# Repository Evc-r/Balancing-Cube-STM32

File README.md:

# STM32F411/ICM-20948 v2 Self-Balancing Cube

Firmware and integration work for a three-axis reaction-wheel balancing cube based on the open-source [remrc/Self-Balancing-Cube](https://github.com/remrc/Self-Balancing-Cube) project.

This version replaces the original ESP32 and MPU6050 with:

- **STM32F411CEU6** microcontroller
- **ICM-20948 v2 breakout** intelligent IMU
- Three **Nidec 24H** reaction-wheel motors with integrated drivers and quadrature encoders
- **3S LiPo** power system

> [!WARNING]
> This project contains high-speed reaction wheels and a LiPo battery. Incorrect PWM polarity, wiring, firmware, or mechanical assembly can cause an unexpected full-power motor start. Read the safety section and complete every diagnostic stage before enabling closed-loop balancing.

## Project status

**Current phase: transitioning into firmware development and software integration.** CAD and the first custom PCB design are complete; electrical bring-up and balancing validation remain ahead.

| Area | Current progress |
|---|---|
| Mechanical design / CAD | Complete for the current build |
| Mechanical assembly | Frame and reaction-wheel assembly completed; final wiring/integration remains |
| Custom four-layer PCB | First design complete and sent for fabrication; known issues require rework and validation |
| STM32 connection | Header spacing mismatch identified; plan to connect the board through wires |
| IMU connection | J7 connector unavailable; plan to solder the IMU wiring directly |
| Firmware | Next active development phase: STM32 project setup, peripheral bring-up, and integration |
| Closed-loop balancing | Not yet demonstrated or validated |

### Current hardware issues

- **Power protection:** an unintended VBAT connection was identified that may bypass the protection stage. A trace-isolation/bodge-wire repair is planned. The repair and its effectiveness have not yet been verified.
- **STM32 header spacing:** the PCB's two long header rows do not match the STM32 board. A wired connection is planned, with a pin-by-pin wiring map and continuity checks before power-up.
- **IMU J7 connection:** direct-soldered wiring is planned because the connector is unavailable. Pin order, logic compatibility, and strain relief still need verification.

These are open integration tasks, not completed fixes. The first PCB revision should not be treated as a validated design for replication.

### Next milestones

1. Document the as-built wiring and verify the PCB rework, power rails, and pin allocation.
2. Create the STM32CubeIDE project and establish basic diagnostics.
3. Bring up safe motor PWM/brake control and validate the encoders.
4. Integrate and characterize the ICM-20948 v2.
5. Implement attitude estimation, calibration, and fault handling.
6. Perform output-limited control tests, then tune vertex balancing.
7. Add edge balancing and usability features after the initial controller is reliable.

See [JOURNAL.md](JOURNAL.md) for retrospective CAD/PCB notes and future session logs, and [PROJECT_PLAN.md](PROJECT_PLAN.md) for the planned architecture and acceptance criteria.

### Documentation and project files

The repository currently contains project documentation, not a buildable firmware release. CAD, KiCad source files, manufacturing outputs, photos, and firmware still need to be added here. The existing [project media folder](https://drive.google.com/drive/folders/1Wyz73s2HkP9Nr1Q7drfzrUGMNGJb-3j-?usp=drive_link) is linked for reference.

Earlier CAD/PCB work is documented retrospectively without reconstructed work hours. Future sessions should record what changed, evidence, test results, and actual tracked time.

## Why this is a firmware port, not a board substitution

The original Arduino/ESP32 sketch cannot be compiled unchanged for this hardware. Several subsystems are fundamentally different:

| Original design | This design |
|---|---|
| ESP32 Arduino | STM32CubeIDE and STM32 HAL |
| MPU6050 raw accelerometer/gyro | ICM-20948 v2 raw accelerometer/gyro with STM32 attitude estimation |
| Original complementary filter | STM32 complementary/Mahony filter using calibrated ICM-20948 data |
| GPIO encoder interrupts | STM32 hardware timer encoder mode |
| ESP32 LEDC PWM | STM32 timer PWM |
| EEPROM API | Versioned internal Flash record with CRC |
| BluetoothSerial | USB CDC or UART initially |
| 15 ms `millis()` loop | Deterministic 200 Hz hardware-timed loop |

The original three-wheel coordinate transformations and controller concept remain useful, but controller gains, timing, calibration, drivers, and safety behavior must be implemented and tested again.

## Hardware

### Required core components

- STM32F411CEU6 board, typically a Black Pill-style board
- ICM-20948 v2 breakout
- Three Nidec 24H motors with integrated motor electronics and encoder outputs
- 3S LiPo battery and suitable connector
- Regulated logic supply appropriate for the selected STM32 board and peripherals
- Motor brake, direction, PWM, and encoder wiring
- Battery-voltage divider
- Active buzzer or another fault indicator
- USB-to-UART adapter if USB CDC is not used
- Physical power disconnect

### Items that must be verified before connection

ICM-20948 v2 breakout and STM32 breakout boards vary. Confirm from the actual boards and schematics:

- STM32 board HSE frequency; this project currently assumes 25 MHz
- ICM-20948 v2 regulator and permitted supply voltage
- ICM-20948 v2 logic voltage, pull-ups, level shifters, and interface-selection pins
- Motor encoder output voltage and whether it is push-pull or open-collector
- Need for external encoder pull-ups
- Maximum battery-divider voltage at a fully charged 3S pack
- Ground continuity between logic, IMU, motors, and battery measurement

Do not assume that a module accepting 5 V power also has 5 V-safe signal pins.

## Planned firmware architecture

The architecture, interfaces, safety behavior, and timing values below are implementation targets. Firmware bring-up, execution timing, and successful balancing have not been verified.

```text
ICM-20948 v2 interrupt
    -> SPI or I2C transfer
    -> register/FIFO driver and sample validation
    -> calibrated accelerometer and gyro sample
    -> STM32 attitude estimator
    -> latest timestamped quaternion and angular rate

200 Hz control timer
    -> validate IMU freshness
    -> read three encoder counters
    -> calculate quaternion balance error
    -> determine vertex, edge, fallen, or fault state
    -> run state-feedback controller
    -> mix X/Y/Z corrections into three wheel commands
    -> update PWM, direction, and brake

Background processing
    -> command interface and telemetry
    -> calibration workflow
    -> Flash parameter storage
    -> battery monitoring
    -> diagnostics and fault reporting
```

Serial output, Flash writes, and blocking IMU transfers must never run inside the control interrupt.

## Clock and timing

A 25 MHz external crystal is assumed for the selected board and still needs confirmation; it is not the intended CPU speed. The STM32F411 will be configured through its PLL for a target system clock of **100 MHz**.

Initial timing targets:

| Function | Target |
|---|---:|
| ICM-20948 accelerometer and gyro sampling | 500 Hz initially |
| STM32 attitude estimator | 500 Hz initially |
| Balance controller | 200 Hz initially |
| Motor PWM | 20 kHz |
| Maximum accepted IMU age | 15 ms initially |

The final CubeMX clock tree must also produce a valid peripheral clock if USB CDC is enabled.

## ICM-20948 v2 approach

The ICM-20948 is a 9-axis IMU containing a 3-axis gyroscope, 3-axis accelerometer, AK09916 3-axis magnetometer, FIFO, programmable filters, and an embedded DMP. It supports SPI up to 7 MHz or I2C up to 400 kHz. The initial controller will read raw accelerometer and gyroscope data and perform attitude estimation on the STM32.

Initial sensing strategy:

- Gyroscope and accelerometer sampled at 500 Hz
- Configurable digital low-pass filtering
- Startup stationary gyro-bias calibration
- Six-axis complementary or Mahony quaternion estimator on the STM32
- Magnetometer disabled for balancing initially because motor currents can disturb it
- DMP integration deferred until the raw-data controller is validated

SPI is preferred for deterministic high-rate acquisition. I2C is acceptable for initial testing if the breakout exposes it more conveniently. Connect and use the data-ready interrupt. Every accepted sample must be timestamped locally, checked for plausibility, and monitored for staleness.

The exact v2 breakout must be inspected for its regulator, level shifting, pull-ups, address selection, and exposed interrupt/chip-select pins. The bare ICM-20948 has lower VDDIO limits than the STM32's 3.3 V logic, so compatibility depends on the breakout circuitry.

## Coordinate frames

All sensor measurements must be transformed into a documented mechanical cube frame before they reach the controller.

The mapping will be bench-tested so that positive physical rotation around cube X, Y, and Z produces positive cube-frame gyro X, Y, and Z respectively. Axis swaps and sign changes will be centralized in one module rather than distributed through the controller.

The wheel numbering, positive rotation direction, encoder sign, and cube-frame force direction will also be documented before closed-loop testing.

## Calibration

The MPU6050 offset procedure will be replaced with two layers: stationary accelerometer/gyro calibration, followed by quaternion reference calibration for the mechanical vertex and edge poses.

The firmware will store:

- Vertex reference quaternion
- Edge reference quaternion
- Sensor-to-cube mapping
- Controller gains
- Battery calibration
- Version, record length, magic value, and CRC32

At runtime the orientation error is calculated from:

```text
q_error = inverse(q_reference) * q_current
```

Calibration will only be accepted when IMU data is fresh, sensor accuracy is acceptable, gyro magnitude is low, and the pose remains stable for a defined interval.

Planned commands:

```text
cal vertex
cal edge
cal status
save
```

An absent, corrupt, or incompatible calibration record must prevent balancing.

## Controller

The controller will retain the reference project's general state-feedback structure while using explicit units:

```text
wheel command =
      angle gain * angle error
    + gyro gain * angular velocity
    + wheel velocity gain * wheel velocity
    + wheel position gain * accumulated wheel position
```

Yaw damping uses vertical-axis gyro and combined wheel motion.

The reference three-wheel transformation will be ported and verified against the actual wheel layout:

```text
m1 = (0.5*x - 0.866*y) / 1.37 + z
m2 = (0.5*x + 0.866*y) / 1.37 + z
m3 = -x / 1.37 + z
```

Original numeric gains will not be copied blindly. The new firmware uses different units, sample timing, sensor latency, encoder scaling, and motor-command scaling.

## Development environment

Planned tools:

- STM32CubeIDE
- STM32CubeMX configuration integrated with CubeIDE
- ST-LINK programmer/debugger
- Git
- Serial terminal
- Multimeter
- Oscilloscope or logic analyzer strongly recommended

The repository will eventually contain the complete CubeIDE project and generated configuration needed for a clean build.

## Planned source layout

```text
Core/Inc/                Public module headers
Core/Src/                Application and driver implementation
Drivers/                 STM32 HAL and device support
Docs/                    Wiring, coordinate frames, calibration, and tuning
Tests/                   Host-side and hardware test support
JOURNAL.md               Retrospective hardware notes and future session logs
PROJECT_PLAN.md          Detailed engineering plan
README.md                 Project overview and bring-up guide
```

## Bring-up order

Do not skip ahead to balance tuning. Each stage is a gate for the next.

### 1. Power and MCU

- Verify every regulated rail without motor output enabled.
- Confirm the STM32 HSE and generated 100 MHz clock.
- Establish UART or USB diagnostics.
- Report firmware version and reset cause at boot.

### 2. Brake and PWM

- Assert brake before PWM initialization.
- Test one motor at a time at a low command limit.
- Verify direction control.
- Measure the real zero-torque PWM polarity.
- Confirm reset and debugger attachment never start a motor.

The reference Nidec interface uses active-low PWM. Treat that as a hypothesis to verify electrically, not an assumption.

### 3. Encoders

- Configure timer encoder mode where possible.
- Verify both channels of each encoder.
- Test direction, stationary noise, wraparound, and maximum speed.
- Document positive directions and counts per revolution.

### 4. ICM-20948 v2

- Verify WHO_AM_I and configure the register banks, ranges, filters, FIFO, and data-ready interrupt.
- Read calibrated accelerometer and gyro samples continuously.
- Run the STM32 attitude estimator and measure sample interval, age, bias, saturation, and communication errors.
- Verify all cube-frame axes.
- Confirm individual motor operation does not interrupt reports.

### 5. Calibration and storage

- Capture stable vertex and edge references.
- Save a versioned record with CRC.
- Verify save, reboot, load, and corrupt-record behavior.

### 6. Output-limited closed-loop testing

- Use a support or tether.
- Apply a low motor-command limit.
- Verify by hand that every correction opposes the fall.
- Test stale-IMU and excessive-tilt shutdown.

### 7. Vertex tuning

- Tune angle feedback.
- Add gyro damping.
- Add wheel-velocity feedback.
- Add a small wheel-position term to prevent saturation.
- Add yaw damping.

### 8. Edge balancing and refinements

Only after vertex balance is reliable:

- Implement edge state detection and reference
- Tune an independent edge controller
- Add wireless tuning
- Add status LEDs and improved telemetry

## Serial interface

Initial transport will be UART or USB CDC. Planned commands include:

```text
help
status
faults
imu
encoders
battery
motor <1|2|3> <command>
motor stop
brake <on|off>
cal vertex
cal edge
cal status
save
set <parameter> <value>
get <parameter>
telemetry <on|off>
```

Manual motor commands will only work in a diagnostic state with the balance controller disabled.

## Safety behavior

The firmware must disable motor output if any of these conditions occurs:

- Boot or calibration is in progress
- IMU data is missing, invalid, saturated, or stale
- ICM-20948 v2 identity/configuration check fails or a reset is detected
- Tilt exceeds the allowed range
- Battery voltage is below the safe threshold
- Encoder plausibility fails
- Control-loop overrun occurs
- A NaN or infinity reaches the controller
- A stop command is received

Physical precautions:

- Wear eye protection during powered tests.
- Use a tether or fixture for initial control tests.
- Keep hands, hair, tools, and loose wiring away from the wheels.
- Secure the LiPo and all connectors mechanically.
- Keep an accessible power disconnect.
- Do not charge the LiPo inside the cube.
- Use independent undervoltage and charging protection appropriate for the pack.
- Never write Flash while the cube is balancing.

## Testing and telemetry

Host-side tests are planned for:

- Quaternion normalization, inversion, and sign handling
- Reference-orientation error
- Coordinate transformations
- Three-wheel mixing and inverse mixing
- Saturation and accumulated-state limits
- Flash record CRC and version checks
- Fault-state transitions

Runtime telemetry will include:

- Control-loop execution time
- IMU sample age and accuracy
- Quaternion and angle errors
- Gyro values
- Encoder deltas and wheel velocities
- Individual controller terms
- Motor commands before and after saturation
- Battery voltage
- Active state and fault flags

## Definition of the first release

Version `v0.1.0` will require:

- A clean build from documented STM32CubeIDE prerequisites
- Documented pin map and wiring
- Passing motor and encoder diagnostics
- Timestamped and fault-monitored ICM-20948 v2 samples and STM32 attitude estimates
- CRC-protected vertex calibration
- Repeatable vertex balance without wheel-speed saturation
- Reliable stale-IMU, over-tilt, low-battery, and software-fault shutdown
- Documented controller units, gains, calibration, and bring-up procedure

Edge balancing may ship in a later release if it is not reliable enough for `v0.1.0`.

## Contributing and development notes

Until the first hardware bring-up is complete, interface definitions, pin assignments, and controller parameters should be considered provisional.

When making changes:

- Keep hardware access separate from control mathematics.
- State physical units in names or comments.
- Do not mix sensor-frame and cube-frame values.
- Include safe defaults and failure behavior.
- Update documentation whenever pin assignments, coordinate signs, or calibration data change.
- Record test conditions and telemetry when changing controller gains.

## Acknowledgements

This project is derived from and inspired by Remigijus's [Self-Balancing-Cube](https://github.com/remrc/Self-Balancing-Cube). The original repository established the mechanical concept, Nidec motor interface, wheel mixing, balance-control structure, and practical build approach.

This repository is an independent STM32F411/ICM-20948 v2 port and will require new firmware, calibration, validation, and gain tuning.

## License

No license has been selected yet. Until a license file is added, normal copyright restrictions apply to original work in this repository. Any reused or adapted material must continue to comply with its original licensing terms.

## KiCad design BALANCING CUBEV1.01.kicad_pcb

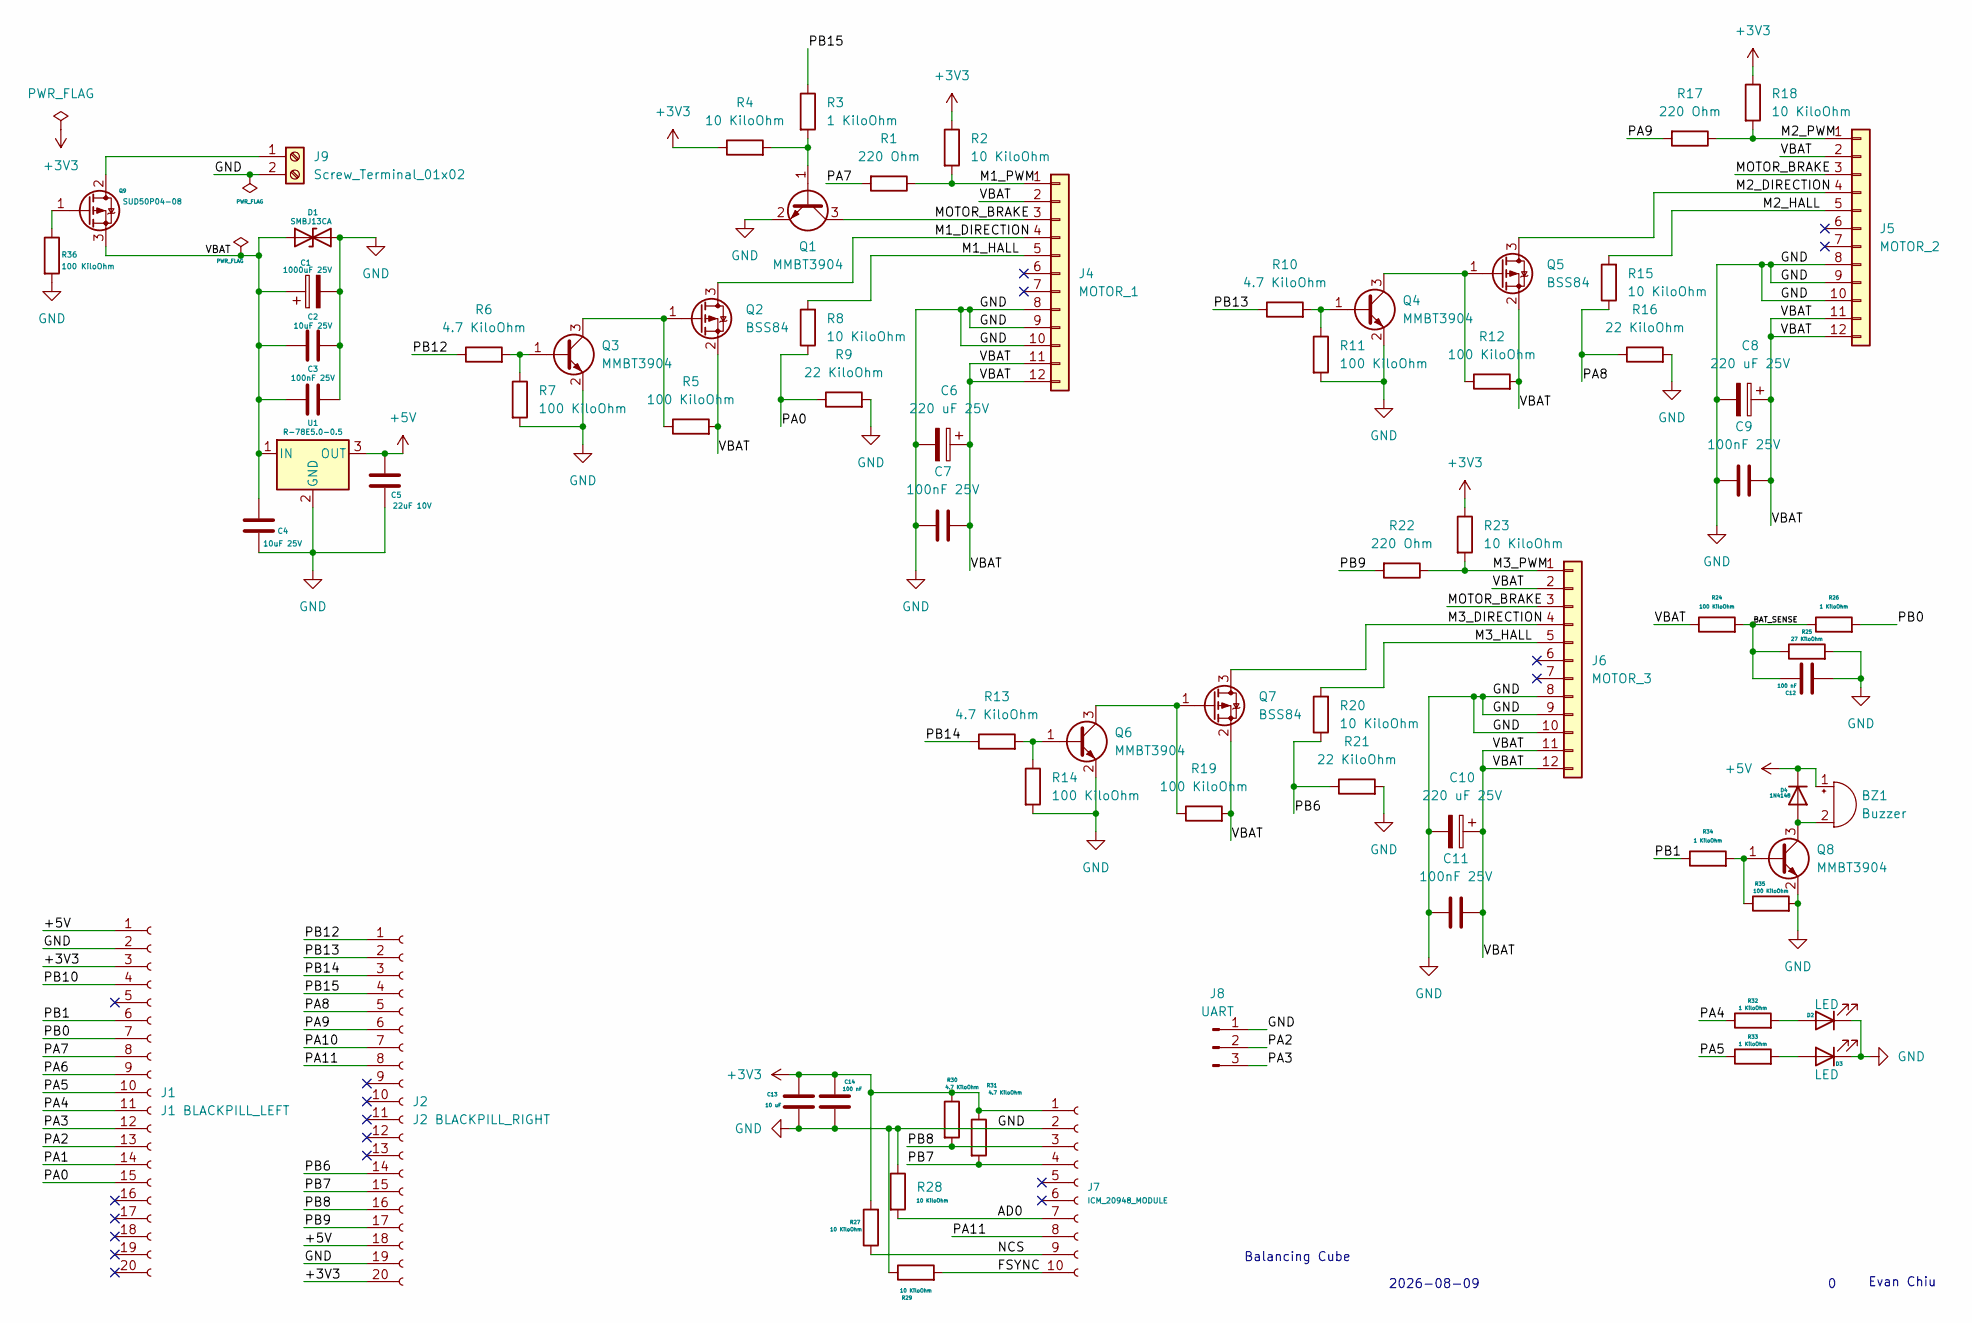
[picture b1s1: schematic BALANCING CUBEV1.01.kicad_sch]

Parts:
BZ1: Buzzer; Buzzer_12x9.5RM7.6
C1: 1000uF 25V; CP_Radial_D12.5mm_P5.00mm
C2, C4: 10uF 25V; C_1210_3225Metric_Pad1.33x2.70mm_HandSolder
C3, C7, C9, C11: 100nF 25V; C_0805_2012Metric_Pad1.18x1.45mm_HandSolder
C5: 22uF 10V; C_1210_3225Metric_Pad1.33x2.70mm_HandSolder
C6, C8, C10: 220 uF 25V; CP_Radial_D8.0mm_P3.50mm
C12, C14: 100 nF; C_0805_2012Metric_Pad1.18x1.45mm_HandSolder
C13: 10 uF; C_1210_3225Metric_Pad1.33x2.70mm_HandSolder
D1: SMBJ13CA; D_SMB
D2, D3: LED; LED_D3.0mm
D4: 1N4148; D_SOD-123
J1: J1 BLACKPILL_LEFT; PinSocket_1x20_P2.54mm_Vertical
J2: J2 BLACKPILL_RIGHT; PinSocket_1x20_P2.54mm_Vertical
J4: MOTOR_1; JST_ZH_B12B-ZR_1x12_P1.50mm_Vertical
J5: MOTOR_2; JST_ZH_B12B-ZR_1x12_P1.50mm_Vertical
J6: MOTOR_3; JST_ZH_B12B-ZR_1x12_P1.50mm_Vertical
J7: ICM_20948_MODULE; PinSocket_1x10_P2.54mm_Horizontal
J8: UART; PinHeader_1x03_P2.54mm_Vertical
J9: Screw_Terminal_01x02; TerminalBlock_Phoenix_MKDS-3-2-5.08_1x02_P5.08mm_Horizontal
Q1, Q3, Q4, Q6, Q8: MMBT3904; SOT-23
Q2, Q5, Q7: BSS84; SOT-23
Q9: SUD50P04-08; TO-252-2
R1, R17, R22: 220 Ohm; R_0805_2012Metric_Pad1.20x1.40mm_HandSolder
R2, R4, R8, R15, R18, R20, R23, R27, R28, R29: 10 KiloOhm; R_0805_2012Metric_Pad1.20x1.40mm_HandSolder
R3, R26, R32, R33, R34: 1 KiloOhm; R_0805_2012Metric_Pad1.20x1.40mm_HandSolder
R5, R7, R11, R12, R14, R19, R24, R35, R36: 100 KiloOhm; R_0805_2012Metric_Pad1.20x1.40mm_HandSolder
R6, R10, R13, R30, R31: 4.7 KiloOhm; R_0805_2012Metric_Pad1.20x1.40mm_HandSolder
R9, R16, R21: 22 KiloOhm; R_0805_2012Metric_Pad1.20x1.40mm_HandSolder
R25: 27 KiloOhm; R_0805_2012Metric_Pad1.20x1.40mm_HandSolder
U1: R-78E5.0-0.5; Converter_DCDC_RECOM_R-78E-0.5_THT

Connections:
+3V3: C13.1, C14.1, J1.3, J2.20, J7.1, R2.1, R4.1, R18.1, R23.1, R27.2, R30.1, R31.1
+5V: BZ1.1 (+), C5.1, D4.1 (K), J1.1, J2.18, U1.3 (OUT)
/AD0: J7.7, R28.2
/BAT_SENSE: C12.1, R24.2, R25.1, R26.1
/FSYNC: J7.10, R29.2
/M1_DIRECTION: J4.4, Q2.3 (D)
/M1_HALL: J4.5, R8.2
/M1_PWM: J4.1, R1.1, R2.2
/M2_DIRECTION: J5.4, Q5.3 (D)
/M2_HALL: J5.5, R15.2
/M2_PWM: J5.1, R17.1, R18.2
/M3_DIRECTION: J6.4, Q7.3 (D)
/M3_HALL: J6.5, R20.2
/M3_PWM: J6.1, R22.1, R23.2
/MOTOR_BRAKE: J4.3, J5.3, J6.3, Q1.3 (C)
/NCS: J7.9, R27.1
/PA0: J1.15, R8.1, R9.1
/PA1: J1.14
/PA2: J1.13, J8.2
/PA3: J1.12, J8.3
/PA4: J1.11, R32.1
/PA5: J1.10, R33.1
/PA6: J1.9
/PA7: J1.8, R1.2
/PA8: J2.5, R15.1, R16.1
/PA9: J2.6, R17.2
/PA10: J2.7
/PA11: J2.8, J7.8
/PB0: J1.7, R26.2
/PB1: J1.6, R34.1
/PB6: J2.14, R20.1, R21.1
/PB7: J2.15, J7.4, R31.2
/PB8: J2.16, J7.3, R30.2
/PB9: J2.17, R22.2
/PB10: J1.4
/PB12: J2.1, R6.1
/PB13: J2.2, R10.1
/PB14: J2.3, R13.1
/PB15: J2.4, R3.1
/VBAT: C1.1, C2.1, C3.1, C4.1, C6.1, C7.2, C8.1, C9.2, C10.1, C11.2, D1.1 (A1), J4.2, J4.11, J4.12, J5.2, J5.11, J5.12, J6.2, J6.11, J6.12, Q2.2 (S), Q5.2 (S), Q7.2 (S), Q9.3 (S), R5.2, R12.2, R19.2, R24.1, U1.1 (IN)
GND: C1.2, C2.2, C3.2, C4.2, C5.2, C6.2, C7.1, C8.2, C9.1, C10.2, C11.1, C12.2, C13.2, C14.2, D1.2 (A2), D2.1 (K), D3.1 (K), J1.2, J2.19, J4.8, J4.9, J4.10, J5.8, J5.9, J5.10, J6.8, J6.9, J6.10, J7.2, J8.1, J9.2, Q1.2 (E), Q3.2 (E), Q4.2 (E), Q6.2 (E), Q8.2 (E), R7.2, R9.2, R11.2, R14.2, R16.2, R21.2, R25.2, R28.1, R29.1, R35.2, R36.2, U1.2 (GND)
unnamed: BZ1.2 (-), D4.2 (A), Q8.3 (C)
unnamed: D2.2 (A), R32.2
unnamed: D3.2 (A), R33.2
unnamed: J9.1, Q9.2 (D)
unnamed: Q1.1 (B), R3.2, R4.2
unnamed: Q2.1 (G), Q3.3 (C), R5.1
unnamed: Q3.1 (B), R6.2, R7.1
unnamed: Q4.1 (B), R10.2, R11.1
unnamed: Q4.3 (C), Q5.1 (G), R12.1
unnamed: Q6.1 (B), R13.2, R14.1
unnamed: Q6.3 (C), Q7.1 (G), R19.1
unnamed: Q8.1 (B), R34.2, R35.1
unnamed: Q9.1 (G), R36.1

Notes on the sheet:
Evan Chiu
2026-08-09
Balancing Cube

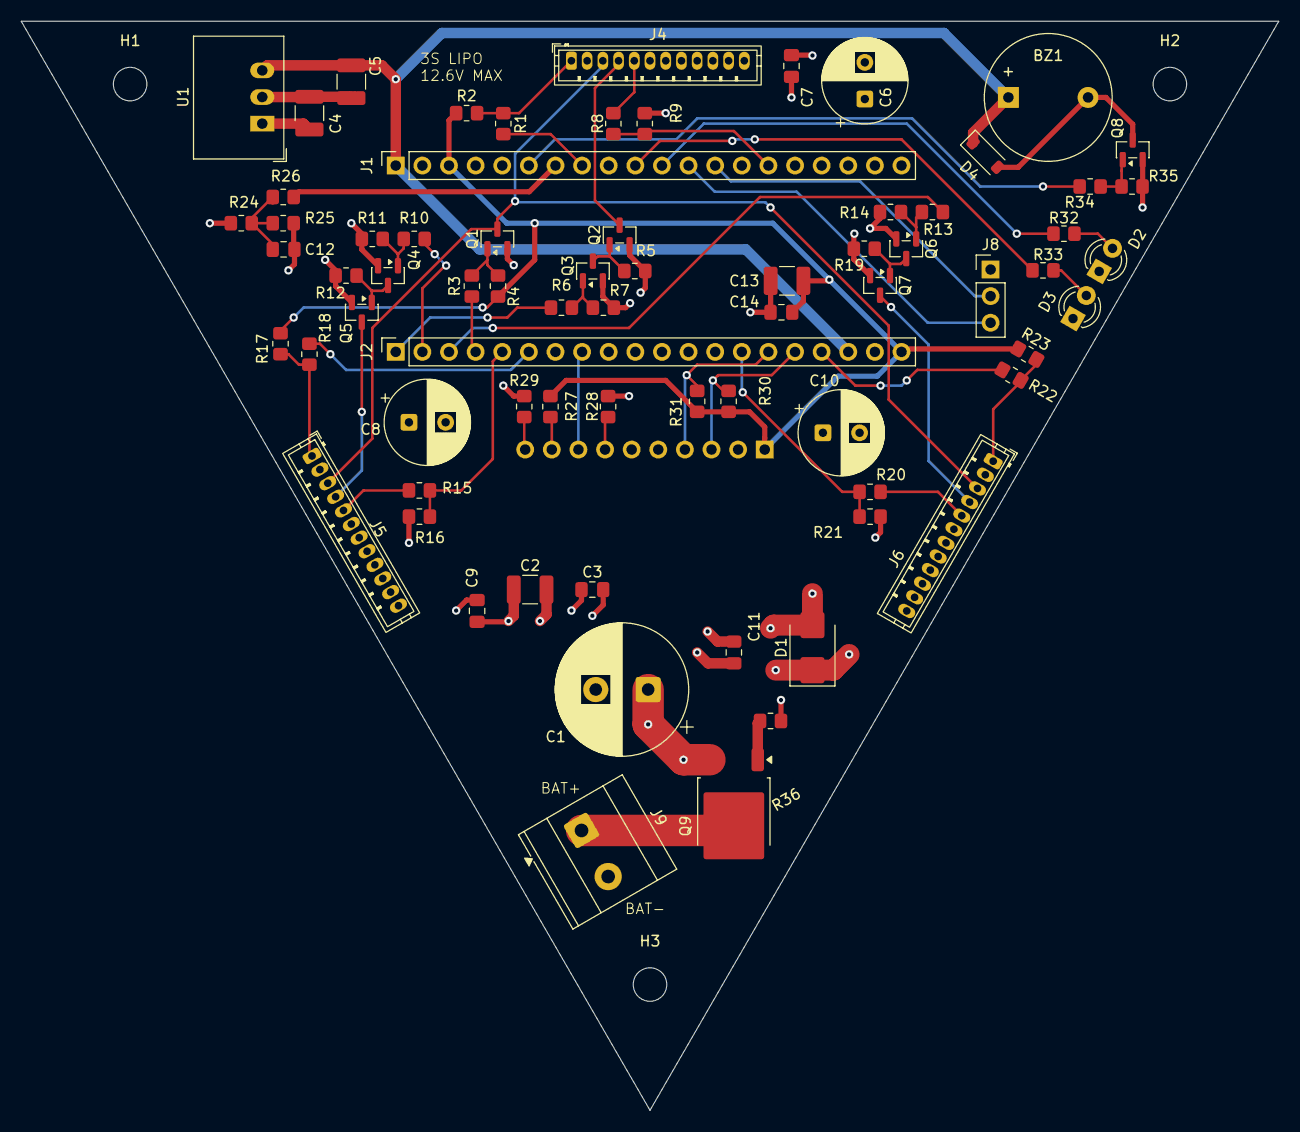
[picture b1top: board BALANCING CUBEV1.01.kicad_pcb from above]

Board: 4 copper layers, 120.0 x 103.9 mm, 76 parts (1 on the bottom side), 50 nets.

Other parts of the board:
H1, H2, H3: MountingHole_3.2mm_M3
